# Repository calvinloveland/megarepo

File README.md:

# Megarepo

A consolidated monorepo for active projects, archived experiments, shared tooling, and repository-level documentation.

## Documentation

Canonical documentation now lives on the GitHub Pages site:

- https://calvinloveland.github.io/megarepo/

Use the web docs for project overviews, repository reference docs, and migrated long-form documentation.

## Repository Layout

- `active/` — maintained projects grouped by area
- `archive/` — historical projects and reference material
- `docs/` — repository-wide source docs for the web site
- `ideas/` — project concepts and brainstorming notes
- `meta/` — repository analysis and maintenance notes
- `scripts/` — automation and documentation tooling

## Contributing

- Start with the web docs: https://calvinloveland.github.io/megarepo/
- Read [PHILOSOPHY.md](PHILOSOPHY.md) for the repo's durable engineering principles.
- Use `python scripts/build_docs_site.py && mkdocs serve` to preview the docs site locally.

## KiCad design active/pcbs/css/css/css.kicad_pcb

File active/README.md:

# Active Projects

This directory now uses the web documentation site as its canonical documentation.

Canonical docs live at:
- https://calvinloveland.github.io/megarepo/projects/active/

Local source docs live in:
- `docs/`

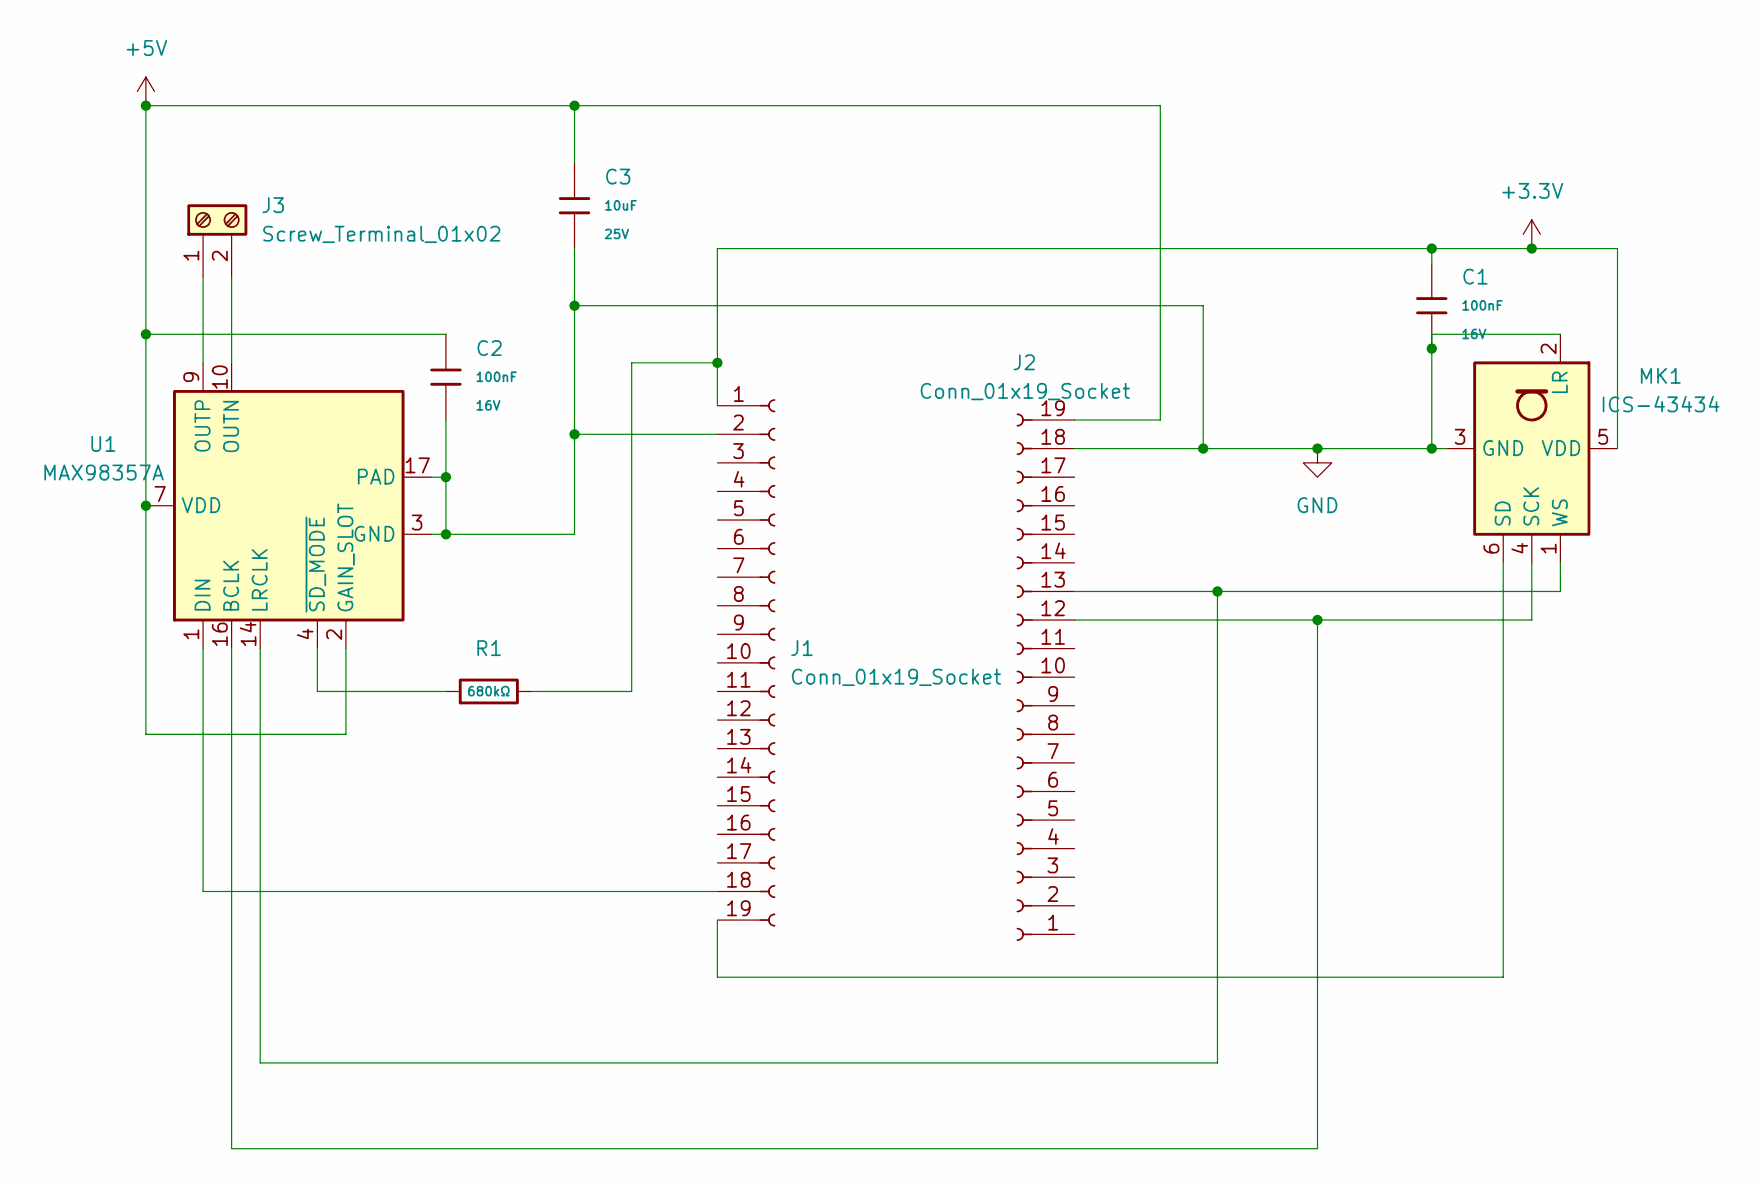
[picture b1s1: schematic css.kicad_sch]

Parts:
C1, C2: 100nF; C_0402; Voltage Rated 16V; Tolerance ±10%; Part CL05B104KO5NNNC; LCSC C1525
C3: 10uF; C_0603; Voltage Rated 25V; Tolerance ±20%; Part CL10A106MA8NRNC; LCSC C96446
J1, J2: Conn_01x19_Socket; PinSocket_1x19_P2.54mm_Vertical
J3: Screw_Terminal_01x02; TerminalBlock_Phoenix_MPT-0,5-2-2.54_1x02_P2.54mm_Horizontal
MK1: ICS-43434; InvenSense_ICS-43434-6_3.5x2.65mm
R1: 680kΩ; R_0603; Overload Voltage (Max) 75V; Tolerance ±1%; Part 0603WAF6803T5E; LCSC C25822
U1: MAX98357A; TQFN-16-1EP_3x3mm_P0.5mm_EP1.23x1.23mm

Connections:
+3.3V: C1.1, J1.1, MK1.5 (VDD), R1.2
+5V: C2.1, C3.1, J2.19, U1.2 (GAIN_SLOT), U1.7 (VDD), U1.8 (VDD)
GND: C1.2, C2.2, C3.2, J1.2, J2.18, MK1.2 (LR), MK1.3 (GND), U1.3 (GND), U1.11 (GND), U1.15 (GND), U1.17 (PAD)
unnamed: J1.18, U1.1 (DIN)
unnamed: J1.19, MK1.6 (SD)
unnamed: J2.12, MK1.4 (SCK), U1.16 (BCLK)
unnamed: J2.13, MK1.1 (WS), U1.14 (LRCLK)
unnamed: J3.1, U1.9 (OUTP)
unnamed: J3.2, U1.10 (OUTN)
unnamed: R1.1, U1.4 (~SD_MODE)

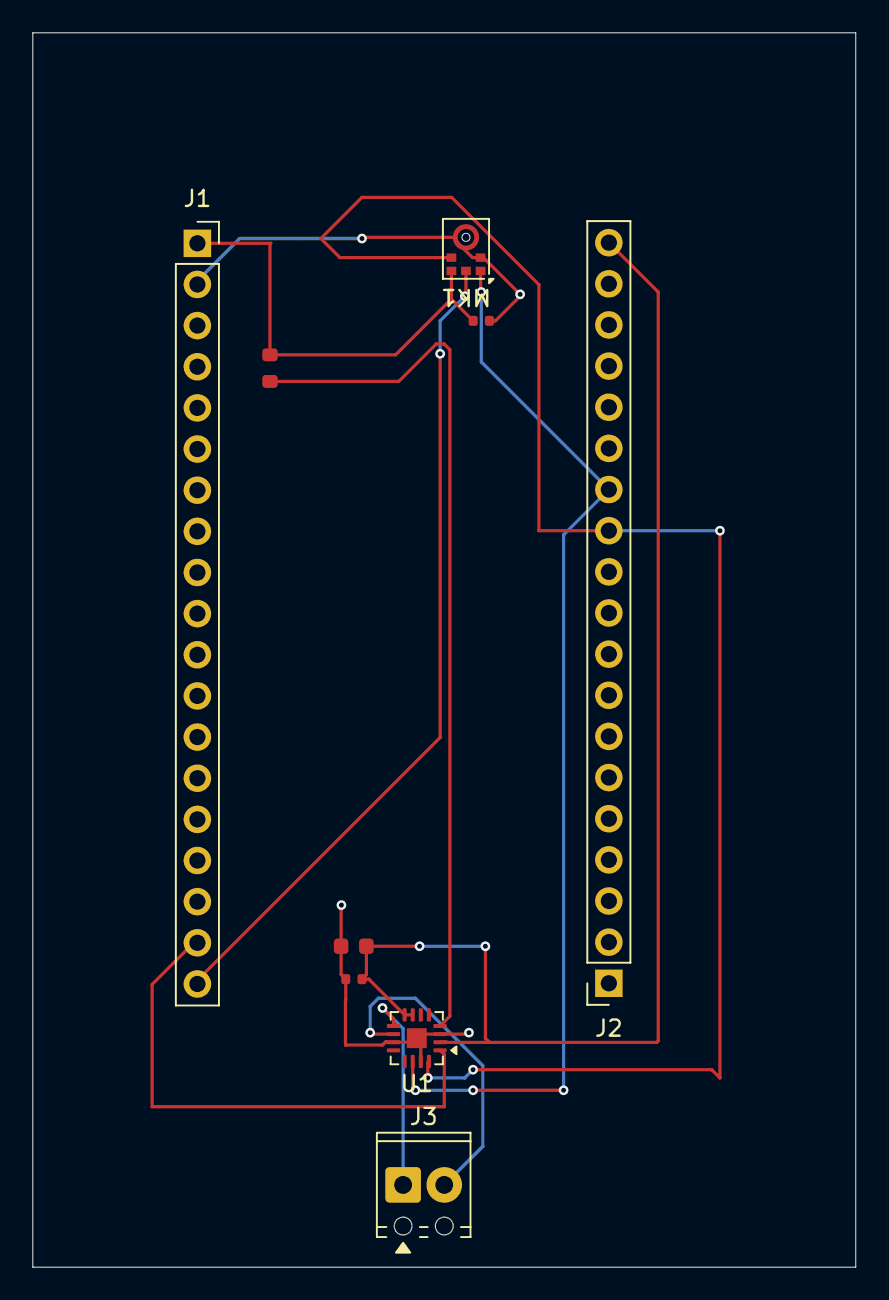
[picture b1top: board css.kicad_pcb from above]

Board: 2 copper layers, 50.8 x 76.2 mm, 9 parts (0 on the bottom side), 10 nets.
